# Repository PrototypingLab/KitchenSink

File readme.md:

# Kitchen Sink

## Kitchen Sink Mini - ESP32-WROOM

### Future Ideas
- Add transistor LED circuit for TX / RX
- Add TVS diode protection circuit

### v1.3 Changelog
- Fixed series capacitor issue on voltage regulators
- Updated power netclass to include RTC battery
- Updated date on silkscreen, added version number

### v1.2 Changelog
- Added solder bridges for selecting IO0 and EN from buttons or (USB-Serial IC and programming header)
- Added 3 additional LEDs on pins designated for shift out
- Moved module closer to edge of board, with space on either side
- Added cutout around module antenna on bottom and top layer
- Added netclass for power traces to be 15 mil
- Updated power traces to 15 mil
- Updated via drill size to be 3 mm
- Updated date on bottom silkscreen

### v1.1 Changelog
- Updated programming header

---------------------

## "Our Programmer"

### v1.1 Changelog
- Added netclass for power traces to be 15 mil
- Updated power traces to 15 mil
- Updated via drill size to be 3 mm
- Updated date on bottom silkscreen

---------------------

## Design Settings
- Trace width: 10 mil
- Power trace width: 15 mil
- Via drill: 3 mm **note units (~ 11.81102 mil)**
- Via annular ring: 10 mil

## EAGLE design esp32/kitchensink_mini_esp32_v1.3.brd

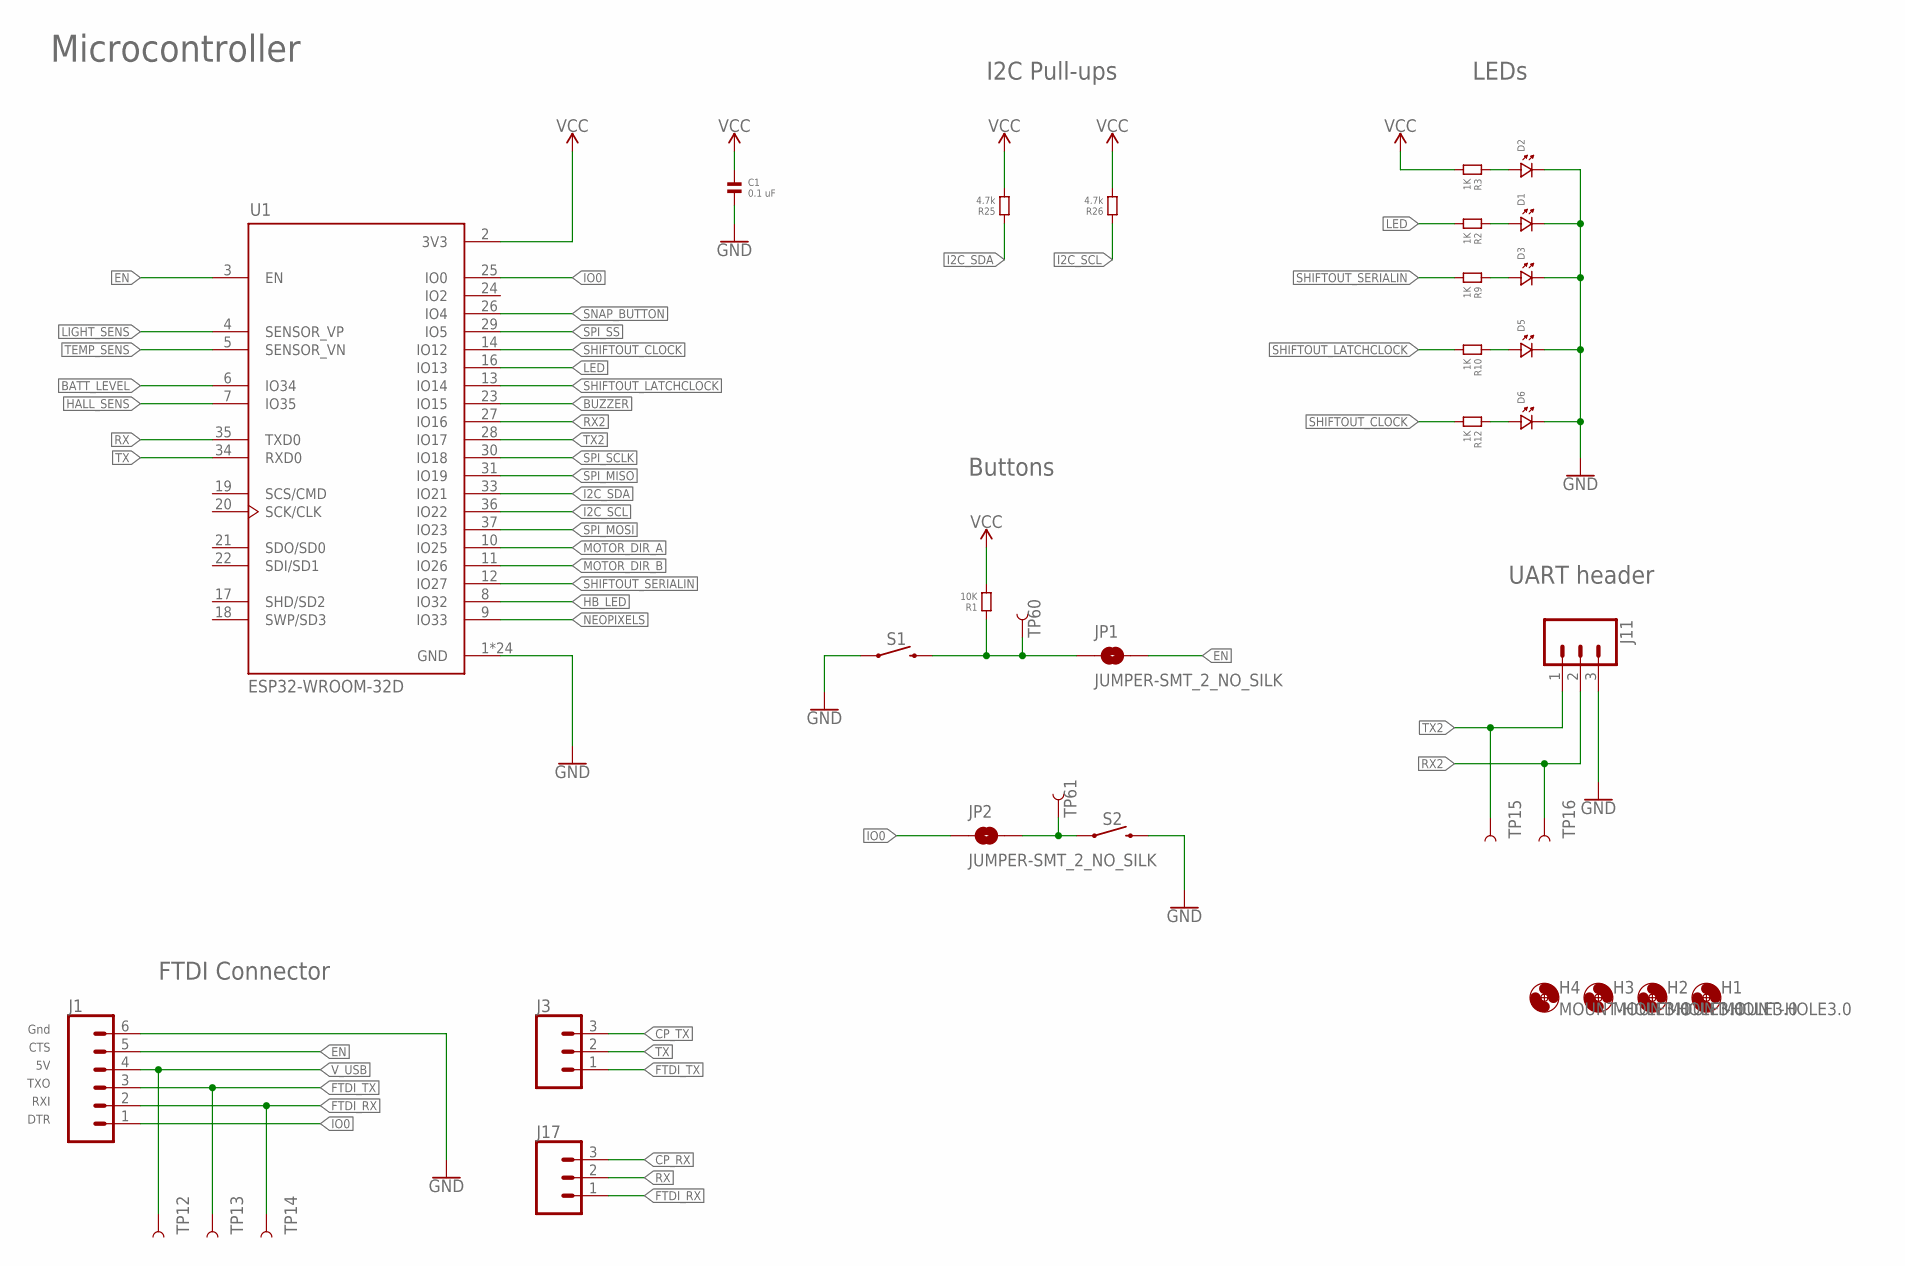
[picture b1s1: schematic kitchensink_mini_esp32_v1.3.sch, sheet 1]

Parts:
C1: 0.1 uF; 1206
D1, D2, D3, D5, D6: LED.1206; 1206.LED
H1, H2, H3, H4: MOUNT-HOLE3.0; 3,0
J1: CONN_06; 1X06-SMD_RA_MALE_NO_HOLES
J3, J17: CONN_03LONGPADS; 1X03_LONGPADS
J11: CONN_03SMD_RA_MALE; 1X03_SMD_RA_MALE
JP1, JP2: JUMPER-SMT_2_NO_SILK; SMT-JUMPER_2_NO_SILK
R1: 10K; 1206
R2, R3, R9, R10, R12: 1K; 1206
R25, R26: 4.7k; 1206
S1, S2: MOMENTARY-SWITCH-SPST-SMD-5.2MM; TACTILE_SWITCH_SMD_5.2MM
TP12, TP13, TP14, TP15, TP16, TP60, TP61: TEST-POINT3X5; PAD.03X.05
U1: ESP32-WROOM-32D; MODULE_ESP32-WROOM-32D

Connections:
BATT_LEVEL: U1.6 (IO34)
BUZZER: U1.23 (IO15); also elsewhere on the board
CP_RX: J17.3; also elsewhere on the board
CP_TX: J3.3; also elsewhere on the board
EN: J1.5, JP1.2, U1.3 (EN); also elsewhere on the board
FTDI_RX: J1.2, J17.1, TP14.P$1
FTDI_TX: J1.3, J3.1, TP13.P$1
GND: D1.P$2 (2), D2.P$2 (2), D3.P$2 (2), D5.P$2 (2), D6.P$2 (2), J1.6, J11.3, S1.1, U1.1 (GND), U1.15 (GND), U1.38 (GND), U1.39_1 (GND), U1.39_2 (GND), U1.39_3 (GND), U1.39_4 (GND), U1.39_5 (GND), U1.39_6 (GND), U1.39_7 (GND), U1.39_8 (GND), U1.39_9 (GND), U1.39_10 (GND), U1.39_11 (GND), U1.39_12 (GND), U1.39_13 (GND), U1.39_14 (GND), U1.39_15 (GND), U1.39_16 (GND), U1.39_17 (GND), U1.39_18 (GND), U1.39_19 (GND), U1.39_20 (GND), U1.39_21 (GND); also elsewhere on the board
HALL_SENS: U1.7 (IO35)
HB_LED: U1.8 (IO32)
I2C_SCL: R26.1, U1.36 (IO22); also elsewhere on the board
I2C_SDA: R25.1, U1.33 (IO21); also elsewhere on the board
IO0: J1.1, JP2.1, U1.25 (IO0); also elsewhere on the board
LED: R2.2, U1.16 (IO13)
LIGHT_SENS: U1.4 (SENSOR_VP); also elsewhere on the board
MOTOR_DIR_A: U1.10 (IO25)
MOTOR_DIR_B: U1.11 (IO26)
unnamed: C1.2, S2.3 (2)
unnamed: D3.P$1 (1), R9.1
unnamed: D1.P$1 (1), R2.1
unnamed: D5.P$1 (1), R10.1
unnamed: D2.P$1 (1), R3.1
unnamed: D6.P$1 (1), R12.1
NEOPIXELS: U1.9 (IO33); also elsewhere on the board
PRE_EN: JP1.1, R1.1, S1.3 (2), TP60.P$1
PRE_IO0: JP2.2, S2.1, TP61.P$1
RX: J17.2, U1.35 (TXD0)
RX2: J11.2, TP16.P$1, U1.27 (IO16)
SHIFTOUT_CLOCK: R12.2, U1.14 (IO12)
SHIFTOUT_LATCHCLOCK: R10.2, U1.13 (IO14)
SHIFTOUT_SERIALIN: R9.2, U1.12 (IO27)
SNAP_BUTTON: U1.26 (IO4); also elsewhere on the board
SPI_MISO: U1.31 (IO19); also elsewhere on the board
SPI_MOSI: U1.37 (IO23); also elsewhere on the board
SPI_SCLK: U1.30 (IO18); also elsewhere on the board
SPI_SS: U1.29 (IO5); also elsewhere on the board
TEMP_SENS: U1.5 (SENSOR_VN); also elsewhere on the board
TX: J3.2, U1.34 (RXD0)
TX2: J11.1, TP15.P$1, U1.28 (IO17)
VCC: R1.2, R3.2, R25.2, R26.2, U1.2 (3V3); also elsewhere on the board
V_USB: J1.4, TP12.P$1; also elsewhere on the board

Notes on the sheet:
Microcontroller
FTDI Connector
I2C Pull-ups
UART header
LEDs
Buttons
Gnd
CTS
TXO
RXI
DTR

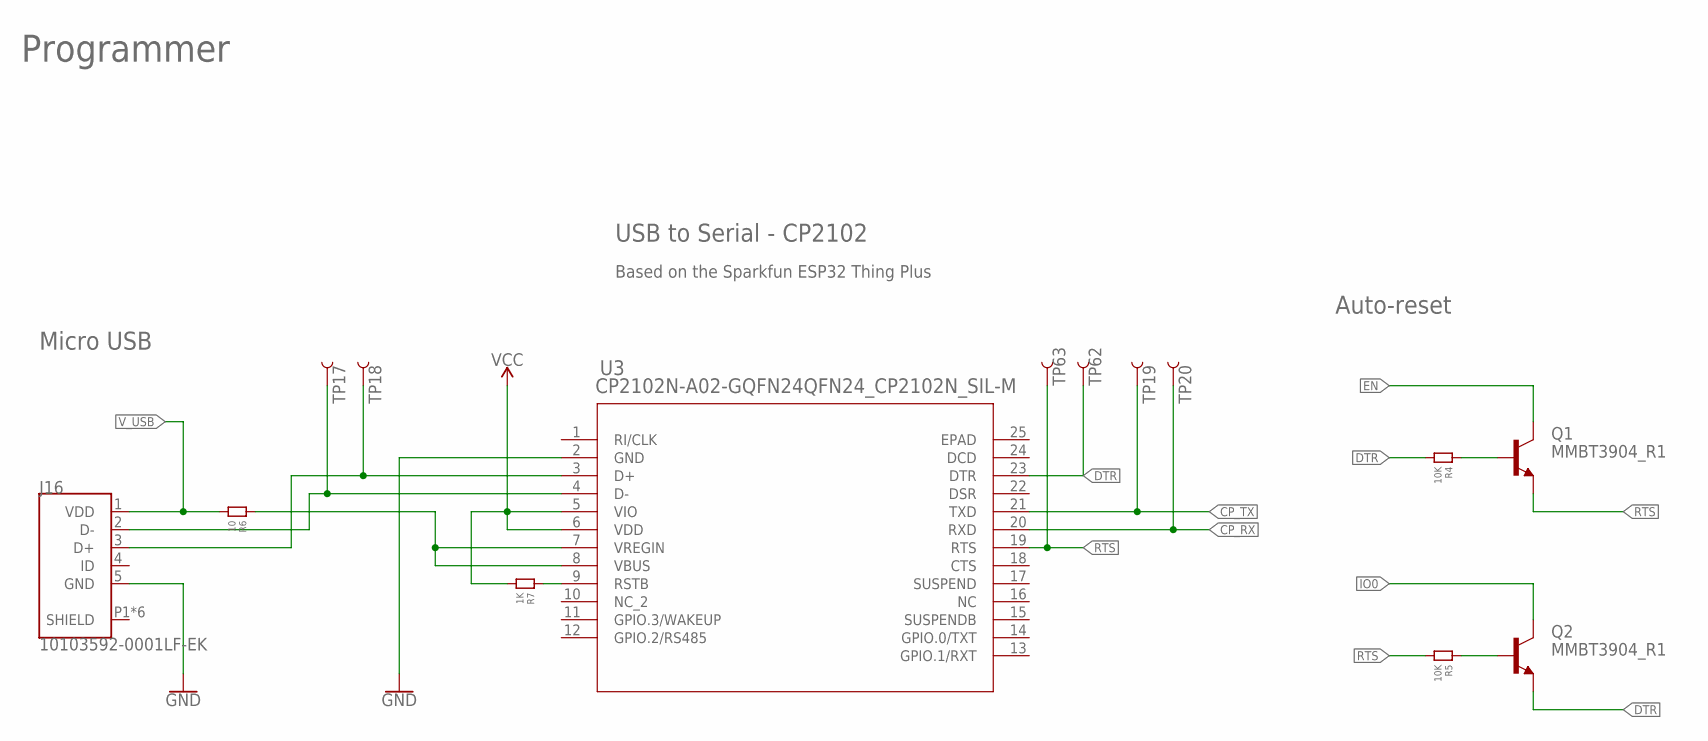
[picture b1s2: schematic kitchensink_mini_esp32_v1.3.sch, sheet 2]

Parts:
J16: 10103592-0001LF-EK; AMPHENOL_10103592-0001LF
Q1, Q2: MMBT3904_R1; SOT23
R4, R5: 10K; 1206
R6: 10; 1206
R7: 1K; 1206
TP17, TP18, TP19, TP20, TP62, TP63: TEST-POINT3X5; PAD.03X.05
U3: CP2102N-A02-GQFN24QFN24_CP2102N_SIL-M; QFN24_CP2102N_SIL-M

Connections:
CP_RX: TP20.P$1, U3.20 (RXD); also elsewhere on the board
CP_TX: TP19.P$1, U3.21 (TXD); also elsewhere on the board
DTR: Q2.2 (E), R4.2, TP62.P$1, U3.23 (DTR)
EN: Q1.3 (C); also elsewhere on the board
GND: J16.5 (GND), U3.2 (GND); also elsewhere on the board
IO0: Q2.3 (C); also elsewhere on the board
unnamed: R6.1, U3.7 (VREGIN), U3.8 (VBUS)
unnamed: J16.3 (D+), TP18.P$1, U3.3 (D+)
unnamed: J16.2 (D-), TP17.P$1, U3.4 (D-)
unnamed: Q1.1 (B), R4.1
unnamed: Q2.1 (B), R5.1
unnamed: R7.1, U3.9 (RSTB)
RTS: Q1.2 (E), R5.2, TP63.P$1, U3.19 (RTS)
SHIELD: J16.P1 (SHIELD), J16.P2 (SHIELD), J16.P3 (SHIELD), J16.P4 (SHIELD), J16.P5 (SHIELD), J16.P6 (SHIELD)
VCC: R7.2, U3.5 (VIO), U3.6 (VDD); also elsewhere on the board
V_USB: J16.1 (VDD), R6.2; also elsewhere on the board

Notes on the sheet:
Programmer
USB to Serial - CP2102
Auto-reset
Micro USB
Based on the Sparkfun ESP32 Thing Plus

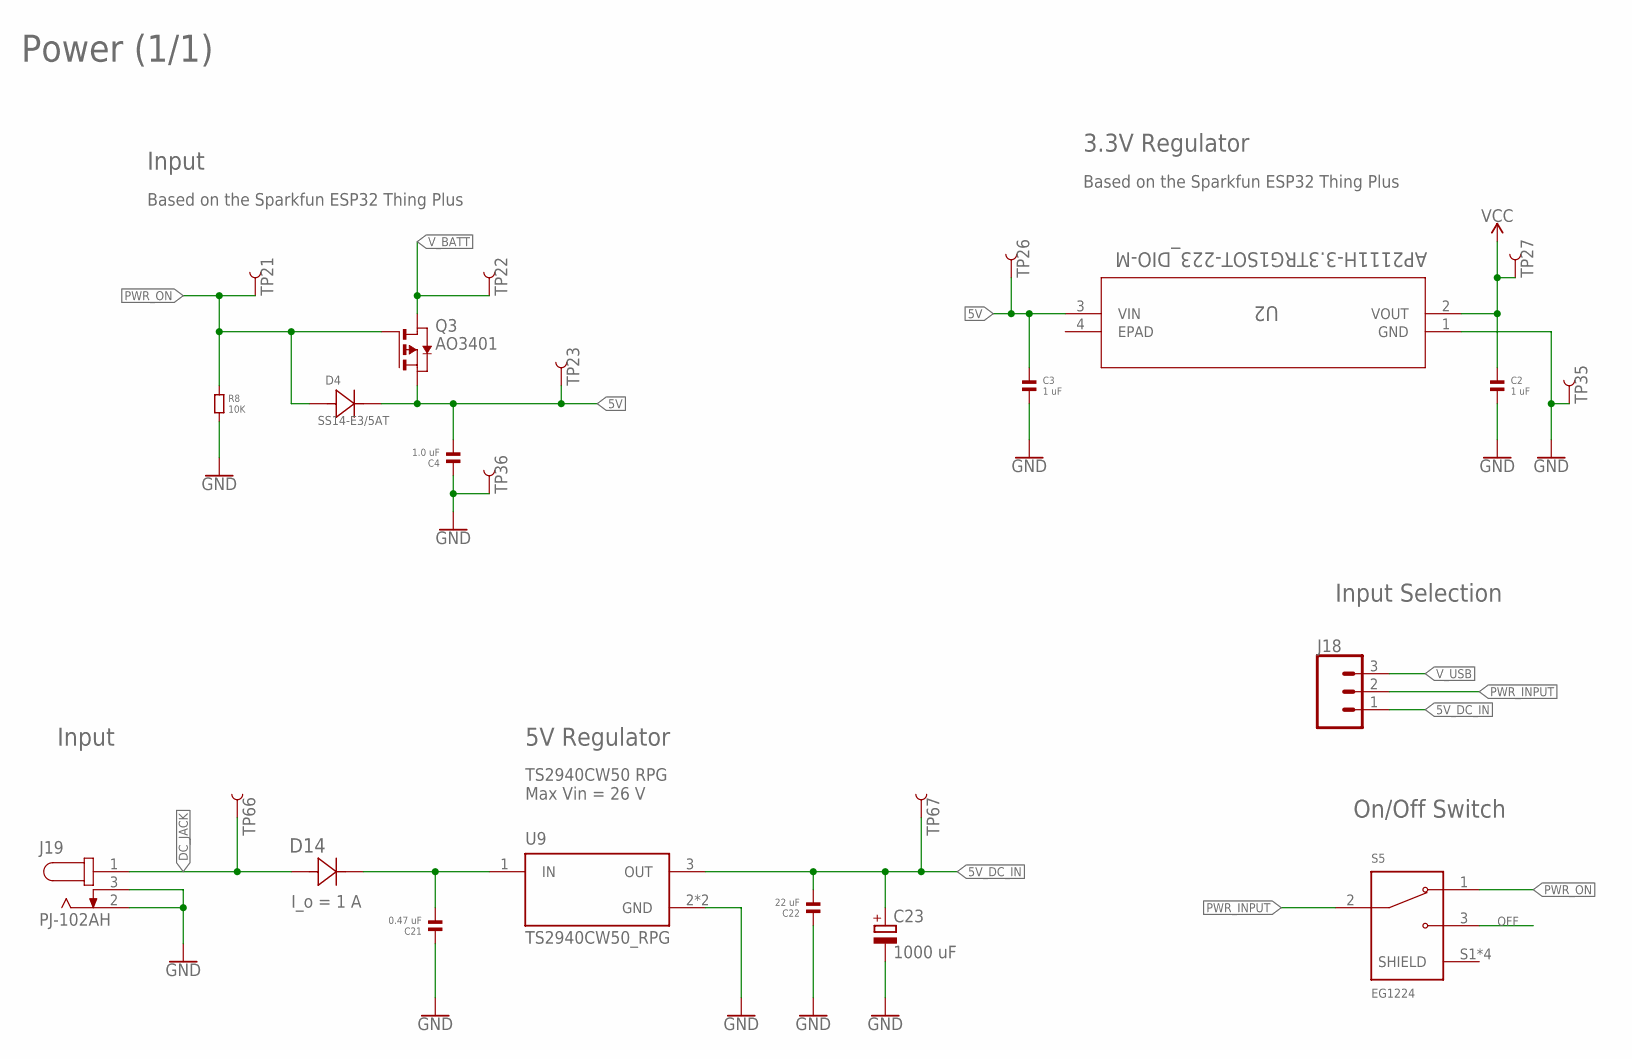
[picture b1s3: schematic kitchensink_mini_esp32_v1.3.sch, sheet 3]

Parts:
C2, C3: 1 uF; 1206
C4: 1.0 uF; 1206
C21: 0.47 uF; 1206
C22: 22 uF; 1206
C23: 1000 uF; 140CLH-1010
D4: SS14-E3/5AT; DIODE_DO214AC
D14: RS1BB-13-FSMA_DIO-M; SMA_DIO-M
J18: CONN_03; 1X03
J19: PJ-102AH; CUI_PJ-102AH
Q3: AO3401; SOT23
R8: 10K; 1206
S5: EG1224; SW_EG1224
TP21, TP22, TP23, TP26, TP27, TP35, TP36, TP66, TP67: TEST-POINT3X5; PAD.03X.05
U2: AP2111H-3.3TRG1SOT-223_DIO-M; SOT-223_DIO-M
U9: TS2940CW50_RPG; VREG_TS2940CW50_RPG

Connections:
5V: C3.1, C4.2, D4.1, Q3.2 (S), TP23.P$1, TP26.P$1, U2.3 (VIN); also elsewhere on the board
5V_DC_IN: C22.2, C23.+, J18.1, TP67.P$1, U9.3 (OUT)
DC_JACK: D14.2, J19.1, TP66.P$1
GND: C2.2, C3.2, C4.1, C21.1, C22.1, C23.-, J19.2, J19.3, R8.2, TP35.P$1, TP36.P$1, U2.1 (GND), U9.2 (GND), U9.4 (GND); also elsewhere on the board
unnamed: C21.2, D14.1, U9.1 (IN)
OFF: S5.3
PWR_INPUT: J18.2, S5.2
PWR_ON: D4.2, Q3.1 (G), R8.1, S5.1, TP21.P$1
VCC: C2.1, TP27.P$1, U2.2 (VOUT); also elsewhere on the board
V_BATT: Q3.3 (D), TP22.P$1
V_USB: J18.3; also elsewhere on the board

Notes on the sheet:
Power (1/1)
Input
Based on the Sparkfun ESP32 Thing Plus
3.3V Regulator
Input Selection
5V Regulator
TS2940CW50 RPG Max Vin = 26 V
I_o = 1 A
On/Off Switch

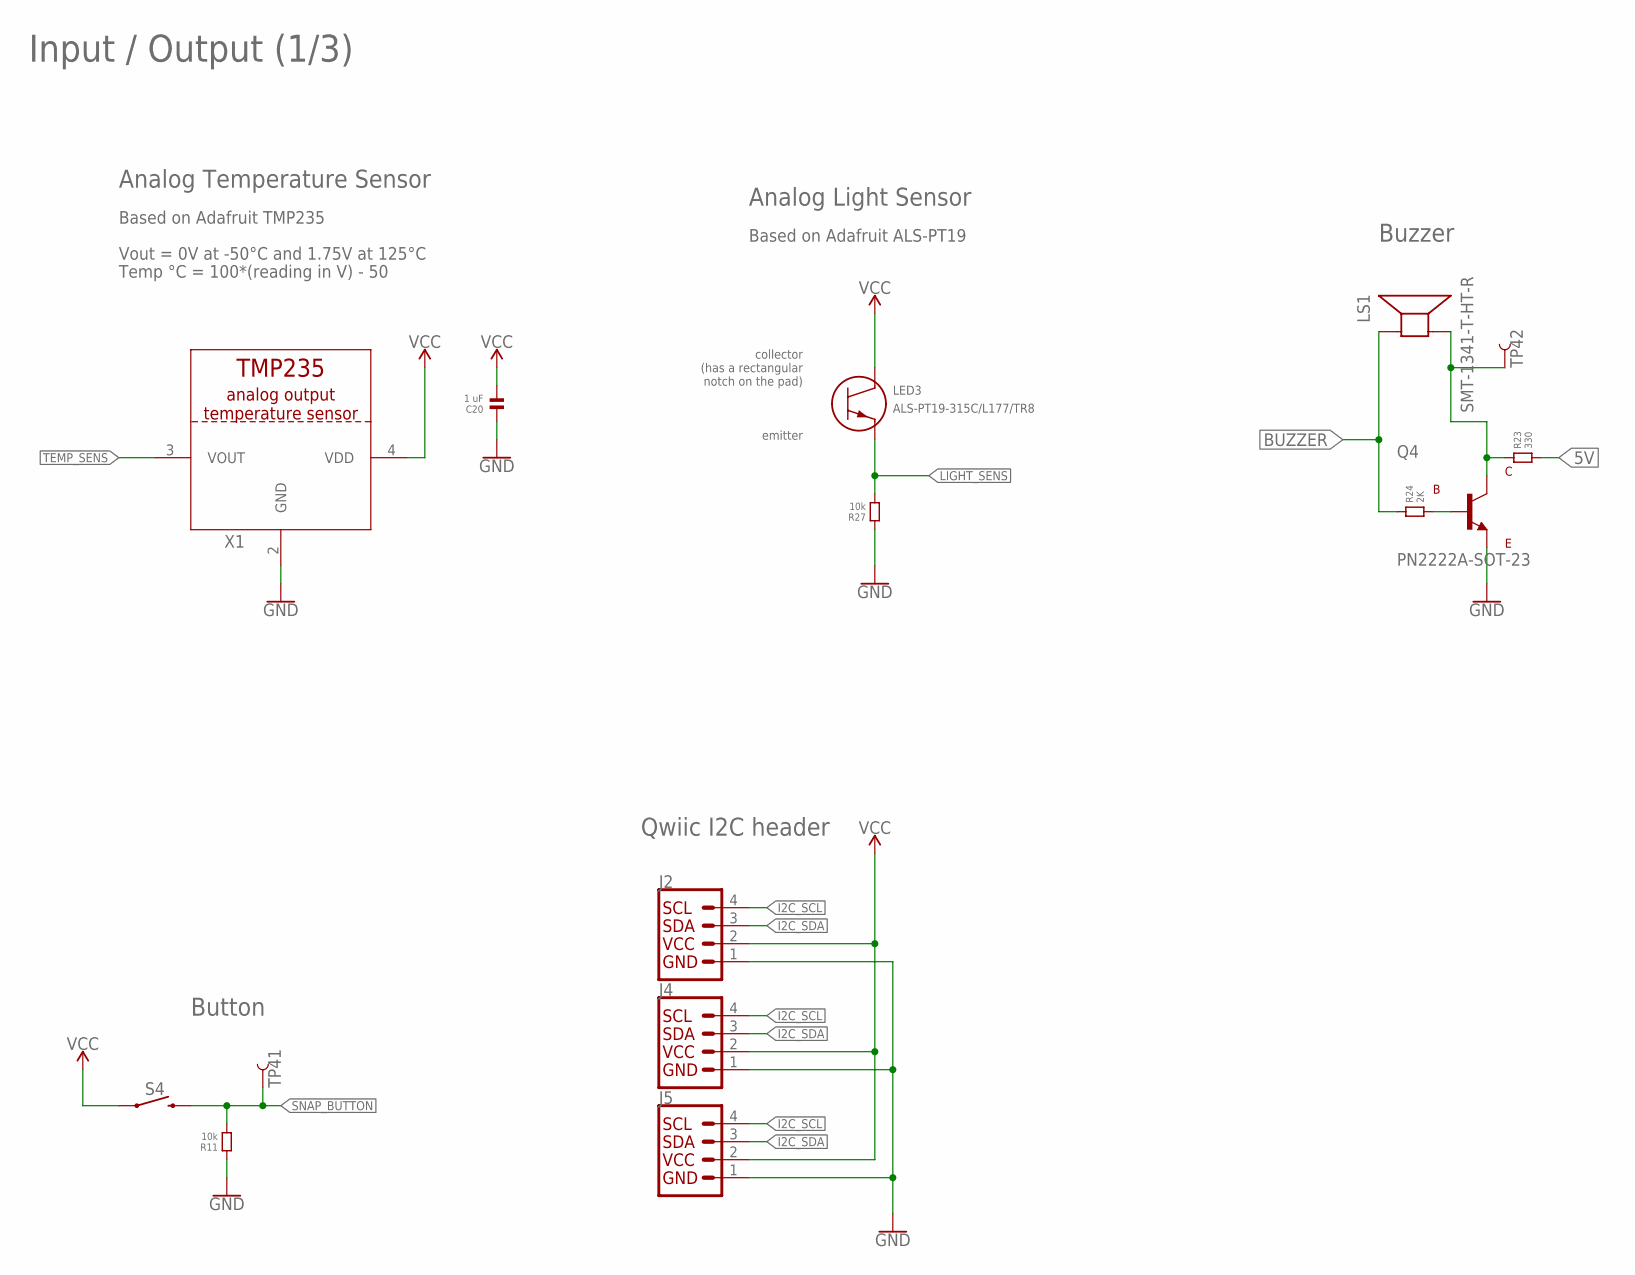
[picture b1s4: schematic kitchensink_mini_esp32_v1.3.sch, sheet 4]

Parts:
C20: 1 uF; 1206
J2, J4, J5: QWIIC_CONNECTORJS-1MM; 1X04_1MM_RA
LED3: ALS-PT19-315C/L177/TR8; LED_77/TR8_EVE
LS1: SMT-1341-T-HT-R; XDCR_SMT-1341-T-HT-R
Q4: PN2222A-SOT-23
R11, R27: 10k; 1206
R23: 330; 1206
R24: 2K; 1206
S4: MOMENTARY-SWITCH-SPST-SMD-5.2MM; TACTILE_SWITCH_SMD_5.2MM
TP41, TP42: TEST-POINT3X5; PAD.03X.05
X1: TMP235_DCKR; SC70-5

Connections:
5V: R23.2; also elsewhere on the board
BUZZER: LS1.P, R24.1; also elsewhere on the board
GND: C20.1, J2.1 (GND), J4.1 (GND), J5.1 (GND), Q4.EMITTER, R11.1, R27.1, X1.2 (GND); also elsewhere on the board
I2C_SCL: J2.4 (SCL), J4.4 (SCL), J5.4 (SCL); also elsewhere on the board
I2C_SDA: J2.3 (SDA), J4.3 (SDA), J5.3 (SDA); also elsewhere on the board
LIGHT_SENS: LED3.2, R27.2; also elsewhere on the board
unnamed: LS1.N, Q4.COLLECTOR, R23.1, TP42.P$1
unnamed: Q4.BASE, R24.2
SNAP_BUTTON: R11.2, S4.3 (2), TP41.P$1; also elsewhere on the board
TEMP_SENS: X1.3 (VOUT); also elsewhere on the board
VCC: C20.2, J2.2 (VCC), J4.2 (VCC), J5.2 (VCC), LED3.1, S4.1, X1.4 (VDD); also elsewhere on the board

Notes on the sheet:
Input / Output (1/3)
Analog Temperature Sensor
Based on Adafruit TMP235
Vout = 0V at -50°C and 1.75V at 125°C
Temp °C = 100*(reading in V) - 50
Analog Light Sensor
collector (has a rectangular notch on the pad)
emitter
Based on Adafruit ALS-PT19
Button
Buzzer
Qwiic I2C header

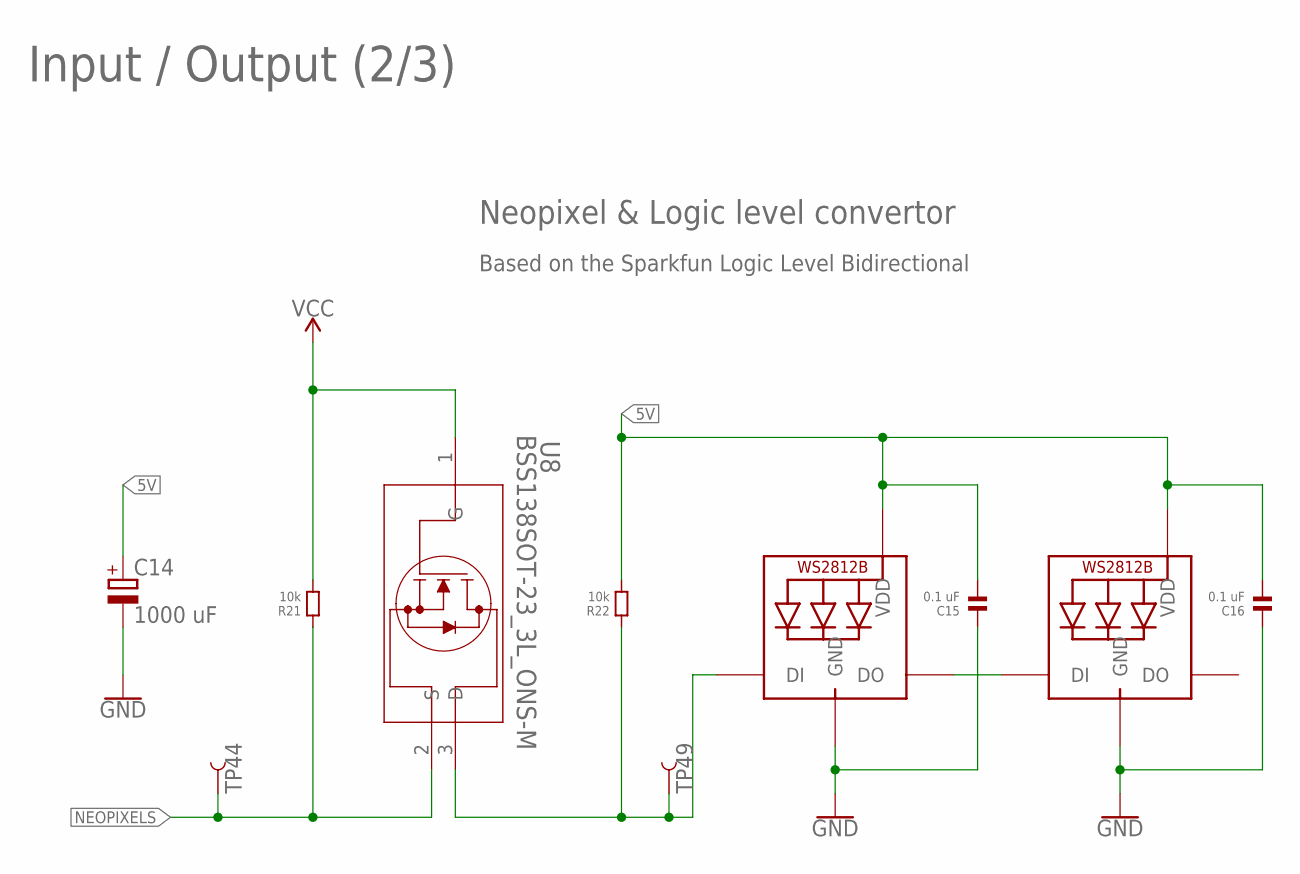
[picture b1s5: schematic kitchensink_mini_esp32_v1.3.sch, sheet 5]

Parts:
C14: 1000 uF; 140CLH-1010
C15, C16: 0.1 uF; 1206
LED1, LED2: WS2812B5050; WS2812B
R21, R22: 10k; 1206
TP44, TP49: TEST-POINT3X5; PAD.03X.05
U8: BSS138SOT-23_3L_ONS-M; SOT-23_3L_ONS-M

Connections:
5V: C14.+, C15.2, C16.2, LED1.1-VDD (VDD), LED2.1-VDD (VDD), R22.2; also elsewhere on the board
GND: C14.-, C15.1, C16.1, LED1.3-GND (GND), LED2.3-GND (GND); also elsewhere on the board
unnamed: LED1.4-DIN (DI), R22.1, TP49.P$1, U8.3 (D)
unnamed: LED1.2-DOUT (DO), LED2.4-DIN (DI)
NEOPIXELS: R21.1, TP44.P$1, U8.2 (S); also elsewhere on the board
VCC: R21.2, U8.1 (G); also elsewhere on the board

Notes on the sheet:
Input / Output (2/3)
Neopixel & Logic level convertor
Based on the Sparkfun Logic Level Bidirectional

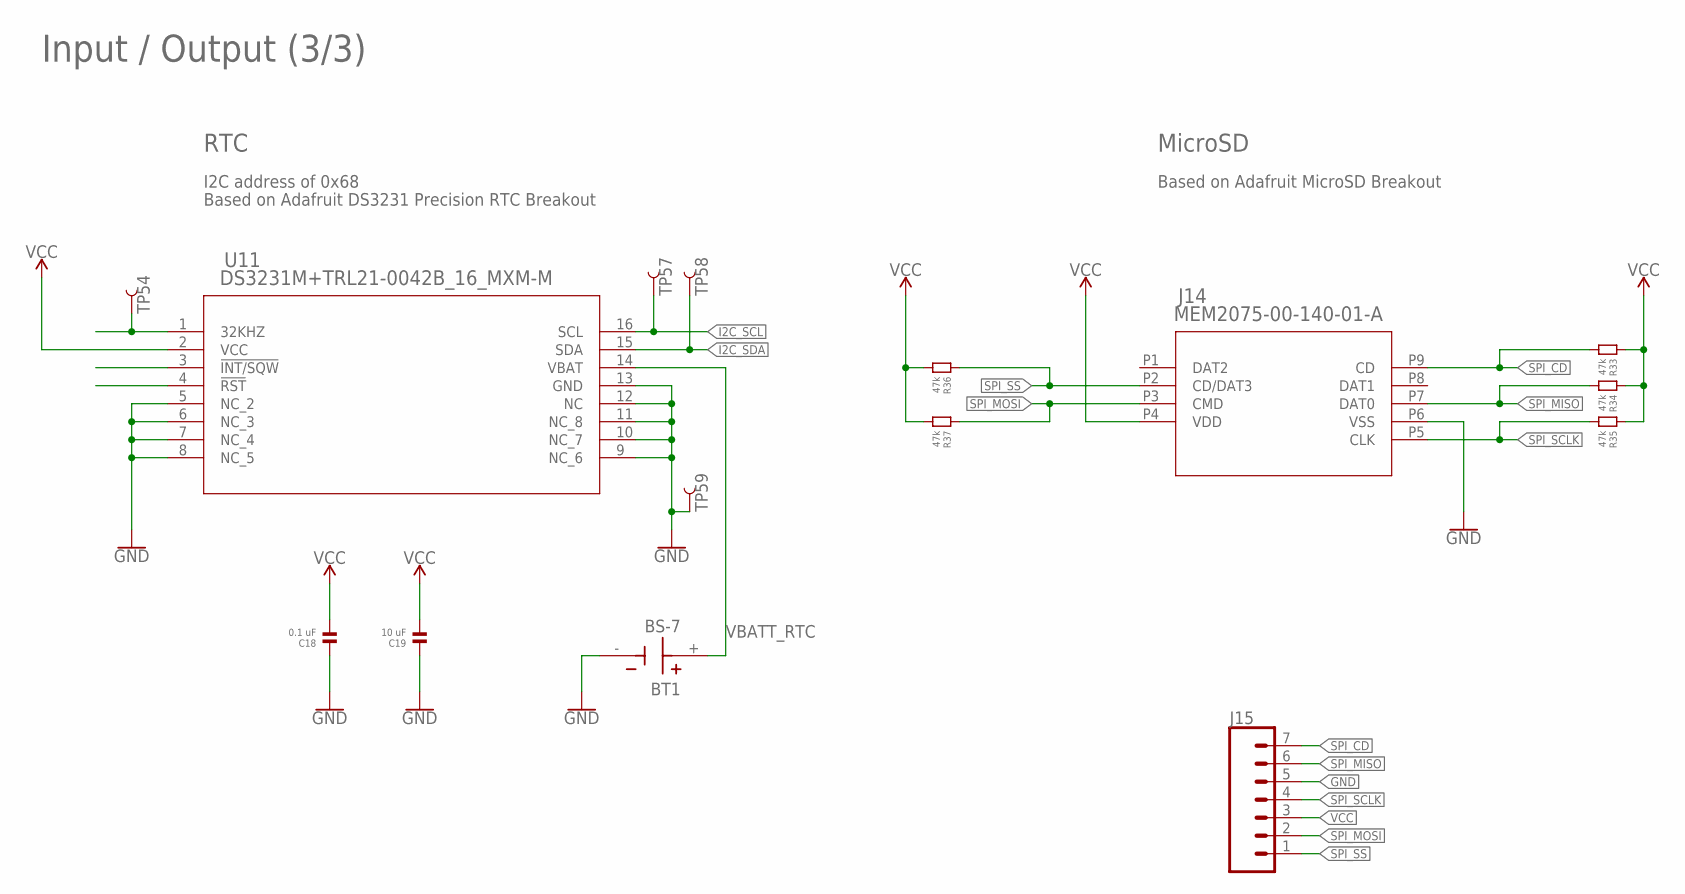
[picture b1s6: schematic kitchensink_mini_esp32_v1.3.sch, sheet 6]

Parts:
BT1: BS-7; BAT_BS-7
C18: 0.1 uF; 1206
C19: 10 uF; 1206
J14: MEM2075-00-140-01-A; MEM2075-00-140-01-A_GCT
J15: CONN_07LONGPADS; 1X07_LONGPADS
R33, R34, R35, R36, R37: 47k; 1206
TP54, TP57, TP58, TP59: TEST-POINT3X5; PAD.03X.05
U11: DS3231M+TRL21-0042B_16_MXM-M; 21-0042B_16_MXM-M

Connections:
GND: BT1.-, C18.1, C19.1, J14.P6 (VSS), J15.5, TP59.P$1, U11.5 (NC_2), U11.6 (NC_3), U11.7 (NC_4), U11.8 (NC_5), U11.9 (NC_6), U11.10 (NC_7), U11.11 (NC_8), U11.12 (NC), U11.13 (GND); also elsewhere on the board
I2C_SCL: TP57.P$1, U11.16 (SCL); also elsewhere on the board
I2C_SDA: TP58.P$1, U11.15 (SDA); also elsewhere on the board
unnamed: TP54.P$1, U11.1 (32KHZ)
SPI_CD: J14.P9 (CD), J15.7, R33.2
SPI_MISO: J14.P7 (DAT0), J15.6, R34.2; also elsewhere on the board
SPI_MOSI: J14.P3 (CMD), J15.2, R37.1; also elsewhere on the board
SPI_SCLK: J14.P5 (CLK), J15.4, R35.2; also elsewhere on the board
SPI_SS: J14.P2 (CD/DAT3), J15.1, R36.1; also elsewhere on the board
VBATT_RTC: BT1.+, U11.14 (VBAT)
VCC: C18.2, C19.2, J14.P4 (VDD), J15.3, R33.1, R34.1, R35.1, R36.2, R37.2, U11.2 (VCC); also elsewhere on the board

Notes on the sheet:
Input / Output (3/3)
RTC
I2C address of 0x68
Based on Adafruit DS3231 Precision RTC Breakout
MicroSD
Based on Adafruit MicroSD Breakout

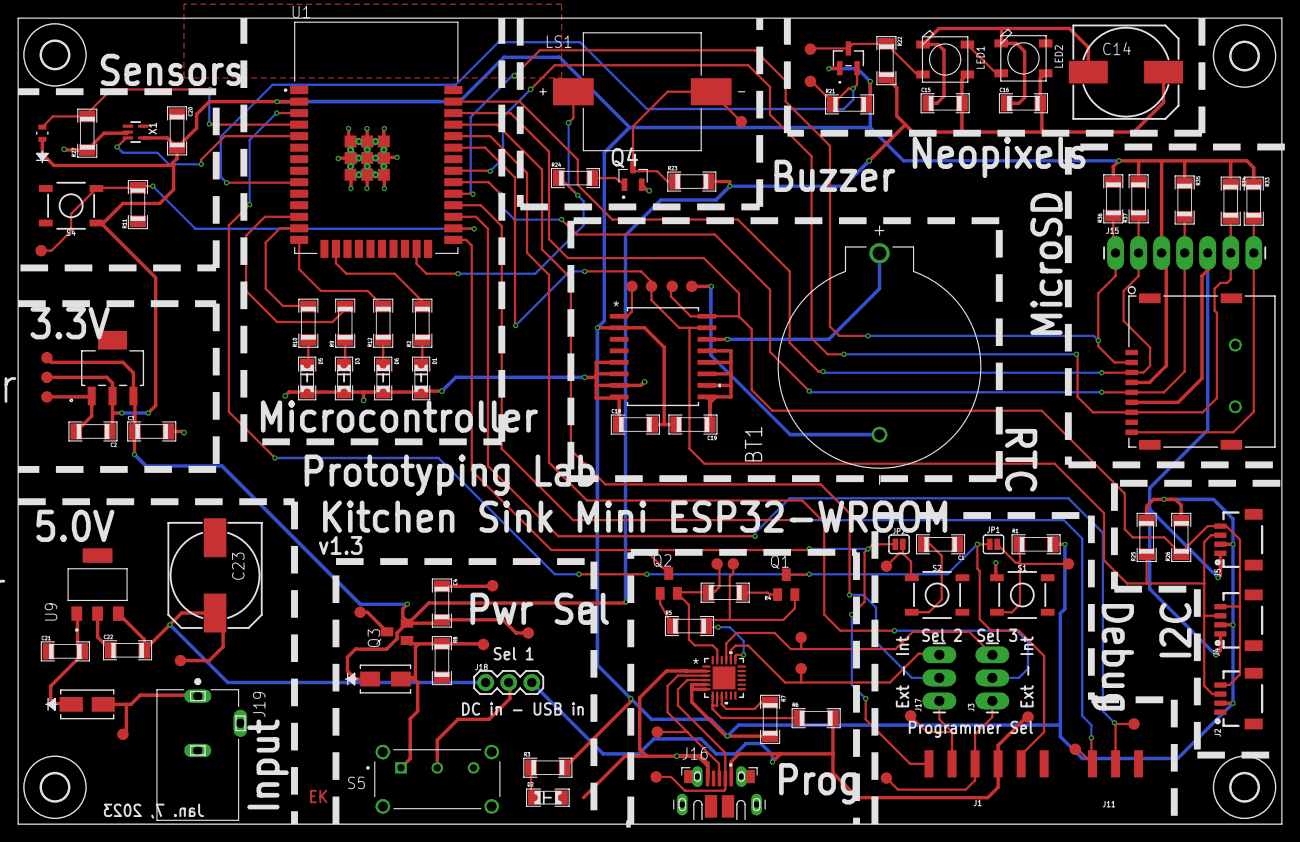
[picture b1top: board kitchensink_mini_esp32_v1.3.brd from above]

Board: 2 copper layers, 139.4 x 88.9 mm, 112 parts (0 on the bottom side), 59 nets.

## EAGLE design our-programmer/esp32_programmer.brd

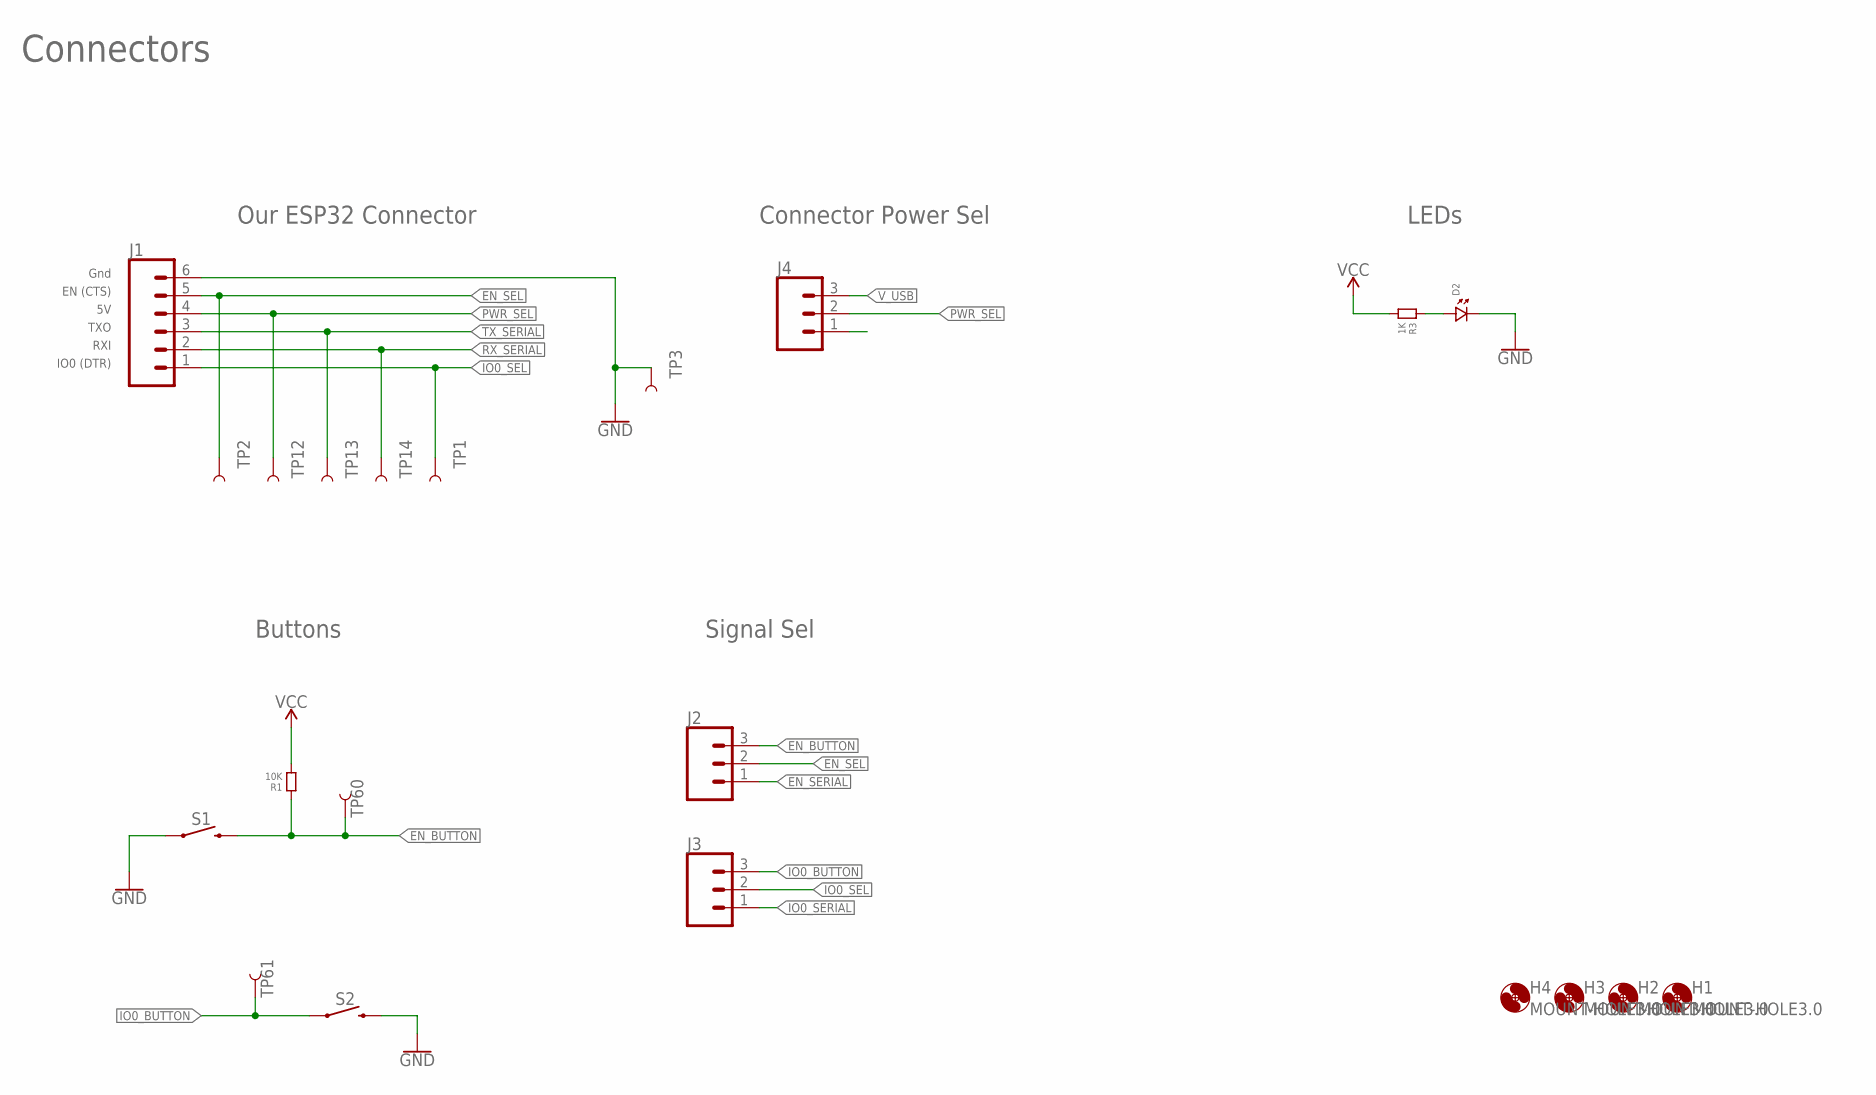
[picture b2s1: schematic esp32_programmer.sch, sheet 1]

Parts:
D2: LED.1206; 1206.LED
H1, H2, H3, H4: MOUNT-HOLE3.0; 3,0
J1: CONN_06LONGPADS; 1X06_LONGPADS
J2, J3, J4: CONN_03LONGPADS; 1X03_LONGPADS
R1: 10K; 1206
R3: 1K; 1206
S1, S2: MOMENTARY-SWITCH-SPST-SMD-5.2MM; TACTILE_SWITCH_SMD_5.2MM
TP1, TP2, TP3, TP12, TP13, TP14, TP60, TP61: TEST-POINT3X5; PAD.03X.05

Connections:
EN_BUTTON: J2.3, R1.1, S1.3 (2), TP60.P$1
EN_SEL: J1.5, J2.2, TP2.P$1
EN_SERIAL: J2.1; also elsewhere on the board
GND: D2.P$2 (2), J1.6, S1.1, S2.3 (2), TP3.P$1; also elsewhere on the board
IO0_BUTTON: J3.3, S2.1, TP61.P$1
IO0_SEL: J1.1, J3.2, TP1.P$1
IO0_SERIAL: J3.1; also elsewhere on the board
unnamed: D2.P$1 (1), R3.1
PWR_SEL: J1.4, J4.2, TP12.P$1
RX_SERIAL: J1.2, TP14.P$1; also elsewhere on the board
TX_SERIAL: J1.3, TP13.P$1; also elsewhere on the board
VCC: R1.2, R3.2; also elsewhere on the board
V_USB: J4.3; also elsewhere on the board

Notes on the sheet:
Our ESP32 Connector
LEDs
Buttons
Gnd
EN (CTS)
TXO
RXI
IO0 (DTR)
Connectors
Connector Power Sel
Signal Sel

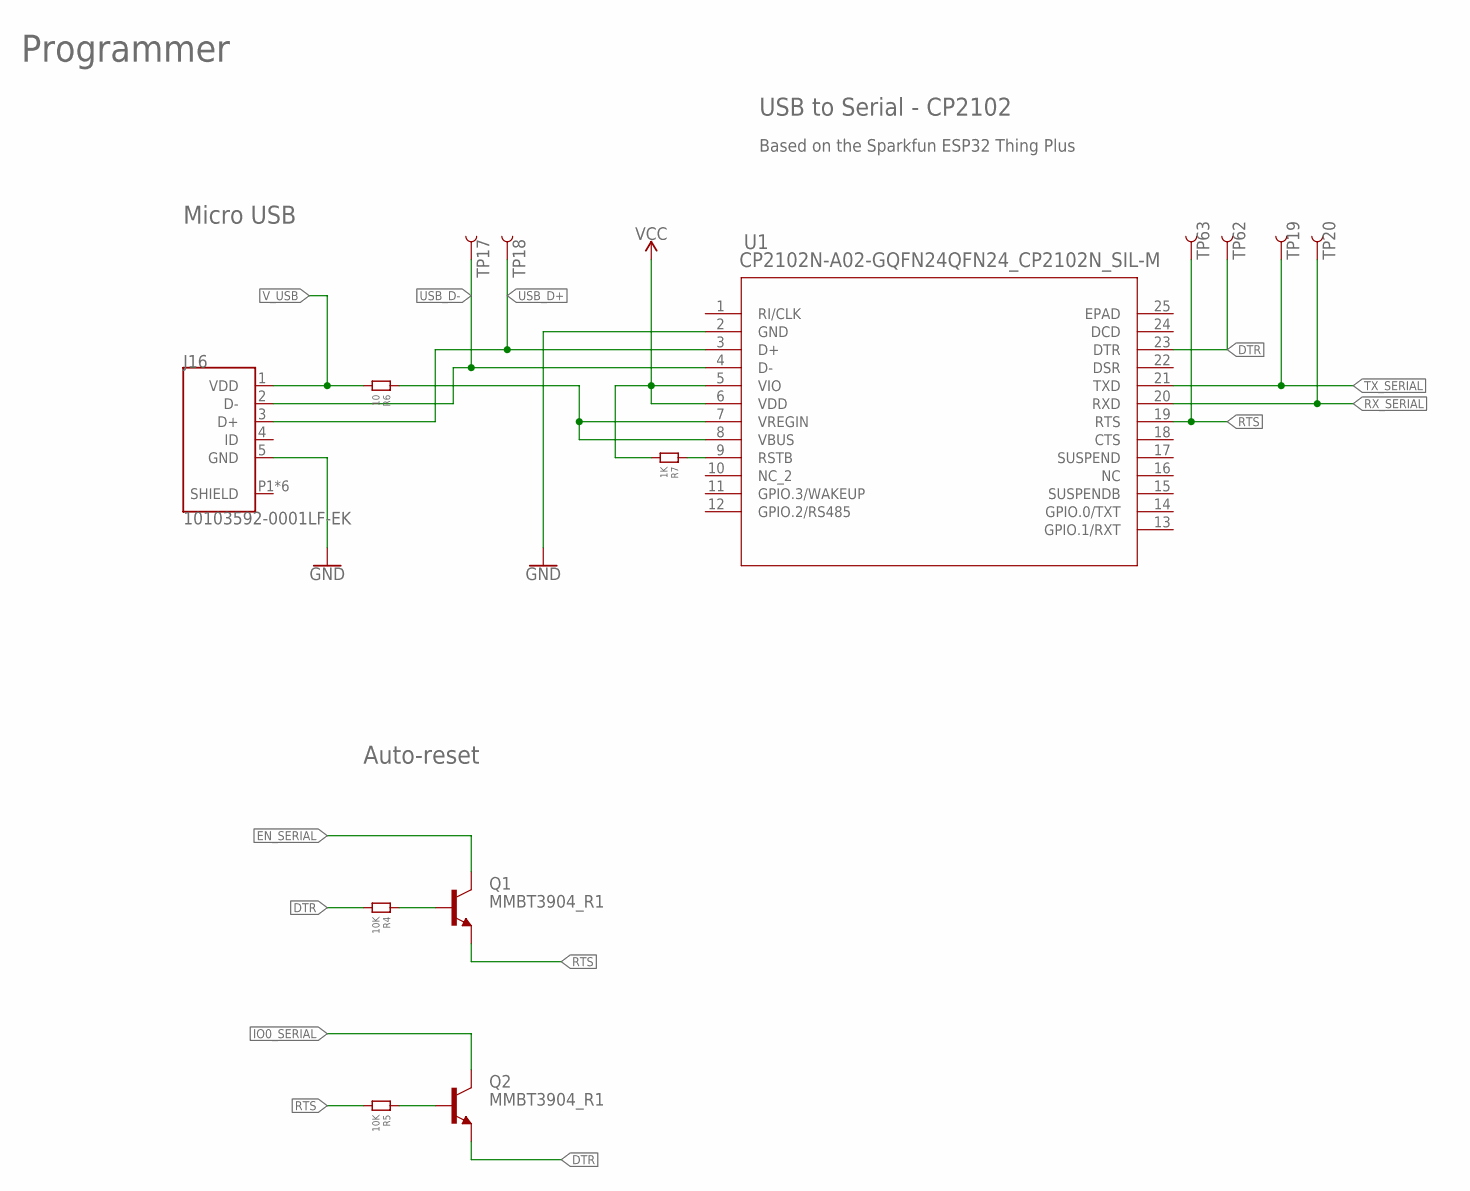
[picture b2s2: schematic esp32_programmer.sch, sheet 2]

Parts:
J16: 10103592-0001LF-EK; AMPHENOL_10103592-0001LF
Q1, Q2: MMBT3904_R1; SOT23
R4, R5: 10K; 1206
R6: 10; 1206
R7: 1K; 1206
TP17, TP18, TP19, TP20, TP62, TP63: TEST-POINT3X5; PAD.03X.05
U1: CP2102N-A02-GQFN24QFN24_CP2102N_SIL-M; QFN24_CP2102N_SIL-M

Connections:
DTR: Q2.2 (E), R4.2, TP62.P$1, U1.23 (DTR)
EN_SERIAL: Q1.3 (C); also elsewhere on the board
GND: J16.5 (GND), U1.2 (GND); also elsewhere on the board
IO0_SERIAL: Q2.3 (C); also elsewhere on the board
unnamed: R6.1, U1.7 (VREGIN), U1.8 (VBUS)
unnamed: Q1.1 (B), R4.1
unnamed: Q2.1 (B), R5.1
unnamed: R7.1, U1.9 (RSTB)
RTS: Q1.2 (E), R5.2, TP63.P$1, U1.19 (RTS)
RX_SERIAL: TP20.P$1, U1.20 (RXD); also elsewhere on the board
SHIELD: J16.P1 (SHIELD), J16.P2 (SHIELD), J16.P3 (SHIELD), J16.P4 (SHIELD), J16.P5 (SHIELD), J16.P6 (SHIELD)
TX_SERIAL: TP19.P$1, U1.21 (TXD); also elsewhere on the board
USB_D+: J16.3 (D+), TP18.P$1, U1.3 (D+); also elsewhere on the board
USB_D-: J16.2 (D-), TP17.P$1, U1.4 (D-); also elsewhere on the board
VCC: R7.2, U1.5 (VIO), U1.6 (VDD); also elsewhere on the board
V_USB: J16.1 (VDD), R6.2; also elsewhere on the board

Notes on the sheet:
Programmer
USB to Serial - CP2102
Auto-reset
Micro USB
Based on the Sparkfun ESP32 Thing Plus

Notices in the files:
parts and their libraries:
SparkFun-Switches: Licensing: Creative Commons ShareAlike 4.0 International - https://creativecommons.org/licenses/by-sa/4.0
COPYRIGHT: Copyright (C) 2022 Ultra Librarian. All rights reserved.
